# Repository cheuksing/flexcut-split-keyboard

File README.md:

# Choc 5×4 split keyboard

One identical 20-key half-PCB design, used twice switch-side up. The key field
is symmetric: cumulative column heights **0, 3, 8, 3, 0 mm**, with **19.05 mm**
pitch. Each half uses the generated solder-only **Choc V1/V2 flex footprint**,
20 bottom-side SOD-523 diodes and **five charlieplex scan nets**. The right-hand
anatomical columns reverse; the physical Choc pin patterns do not flip.

The sole PCB definition and output is **`choc5x4_panel`**, the unrouted
98.20×99.475 mm breakaway panel containing one half and the XIAO SAMD21 adapter.
Each component placement is defined once. Checks and drawings extract the half
and adapter directly from this panel. The adapter has headers, two upright USB-C
ports, series/contact isolation resistors and TVS only. All SMD assembly parts,
including the ports and matrix diodes, are on the bottom; switches and the XIAO
are fitted separately on top. No extra regulator or
active protector. Selected USB-C groups preserve identity in all four modeled
plug orientations. Scan margins, rollover and powered/unpowered fault safety
remain on [electrical hold](docs/usb-c-interface-verification.md).
Native KiCad ERC/DRC and complete case construction remain open.

## Build and review

To use the local Ergogen web interface after `npm ci`:

```sh
npm run dev
```

Open **http://127.0.0.1:8787**. The editor loads `ergogen/config.yaml` and the
project's custom switch/diode footprints. It generates key positions, outlines
and a PCB preview, with zoom/pan and YAML, SVG, DXF, JSON and KiCad downloads.
Drafts stay in memory; downloading YAML does not overwrite the project file.
Invalid edits show generation errors while clearly marking the last preview as
outdated. The checked matrix review is available from the header.

The server binds to this computer only, uses the pinned local Ergogen engine and
needs no external service. Change the port with `PORT=8788 npm run dev`. Stop it
with Ctrl+C. Web generation is a preview, not a manufacturing check: after saving
an edited configuration into the project, run `npm run review`.

Requires Node.js 22+ and Python/Shapely. Install pinned Node dependencies and the
geometry dependency once:

```sh
npm ci
python3 -m venv .venv-manufacturing
.venv-manufacturing/bin/python -m pip install -r scripts/requirements-manufacturing.txt
npm run review
```

For another Python environment, set `MANUFACTURING_PYTHON` to its interpreter.
The following are local review artifacts; the workflow uses no browser or GUI:

- [Keyboard review](build/keyboard/index.html), [layout PNG](build/keyboard/layout.png),
  [matrix PNG](build/keyboard/matrix.png), [support concepts](build/keyboard/supports.png).
- [Panel KiCad PCB](build/keyboard/choc5x4_panel.kicad_pcb) and
  [half schematic](build/keyboard/choc5x4_half.kicad_sch).
- [Directed-pair CSV](build/keyboard/matrix.csv) and [key placements](build/keyboard/keys.json).
- [All three switch footprints](build/review/index.html) and their generated
  `build/review/SwitchFlex.pretty/` library.
- [Exact-input verification](docs/manufacturing-verification.md) and
  [constraint register](docs/manufacturing-limitations.md).
- [Actual panel](build/keyboard/panel-fit.svg), [adapter placement](build/keyboard/adapter.svg),
  [adapter schematic](build/keyboard/adapter.kicad_sch).
  Mount the XIAO on two six-pin headers after detaching the adapter; the module overhangs the carrier.

`npm run check` rebuilds all footprints and the keyboard, tests actual schematic
connectivity against PCB pad nets, and checks all three 3×3 fixtures **plus the
complete staggered half, adapter and actual panel**. It also rechecks derived continuous gasket/rib concepts.
`npm run review` runs that full gate before emitting drawings. Ordinary drawing
checks do not establish native KiCad, CAM, fatigue or price approval.

`npm run check:interface` writes the USB-C electrical report and exits nonzero
while scan margins, rollover and protection remain unresolved.
This electrical release gate is separate from the geometry checks above.

`npm run build:keyboard` emits CAD without the manufacturing gate. Use the npm
runner: it sets PCB thickness to **1.2 mm**; the bare Ergogen KiCad 8 CLI template
defaults to 1.6 mm. Generated `*.kicad*` files under `build/` are committed so
they can be previewed in KiCanvas; other build outputs remain ignored and can be
recreated with `npm run review`.

## Design sources

```text
ergogen/config.yaml               Sole panel PCB definition; shared half/adapter outlines
ergogen/footprints/choc.js         Generated Choc V1/V2 footprint, unchanged pin/cut geometry
ergogen/footprints/diode_sod523.js  Bottom-side diode land pattern; candidate SKU pending
ergogen/fixtures/                  Preserved original single-key coupon configuration
scripts/build-keyboard.js          Ergogen runner, thickness, CAD, net map and local library
scripts/lib/keyboard-schematic.js  Embedded-symbol KiCad matrix schematic generator
scripts/lib/keyboard.js            Readers and electrical connectivity checks
scripts/lib/board-views.js         Extract half/adapter review geometry from the panel
scripts/check-keyboard.py          Actual staggered-board and support geometry screens
scripts/lib/manufacturing-rules.json  Numeric fabrication/project guards
scripts/build-keyboard-review.js   Offline SVG/PNG/HTML keyboard review
scripts/serve-ergogen.js           Loopback-only web editor and in-memory generation API
web/                              Local YAML editor, interactive preview and downloads
keyboard-flex-study/               Original per-key suspension research and drawings
docs/keyboard.md                  Circuit, reuse, placement and remaining work
```

The library also retains KS-33 and MX footprints. Edit switch geometry in
`scripts/lib/switches.js` and `scripts/lib/footprint-template.js`, then regenerate
and check. Do not hand-edit generated switch modules or scale their flex cuts to
smaller Choc pitch. All switch solder copper/mask stays on B.Cu/B.Mask only;
electrical and V2 mechanical holes remain plated, plastic posts unplated, and the
V2 support unnumbered/unconnected.

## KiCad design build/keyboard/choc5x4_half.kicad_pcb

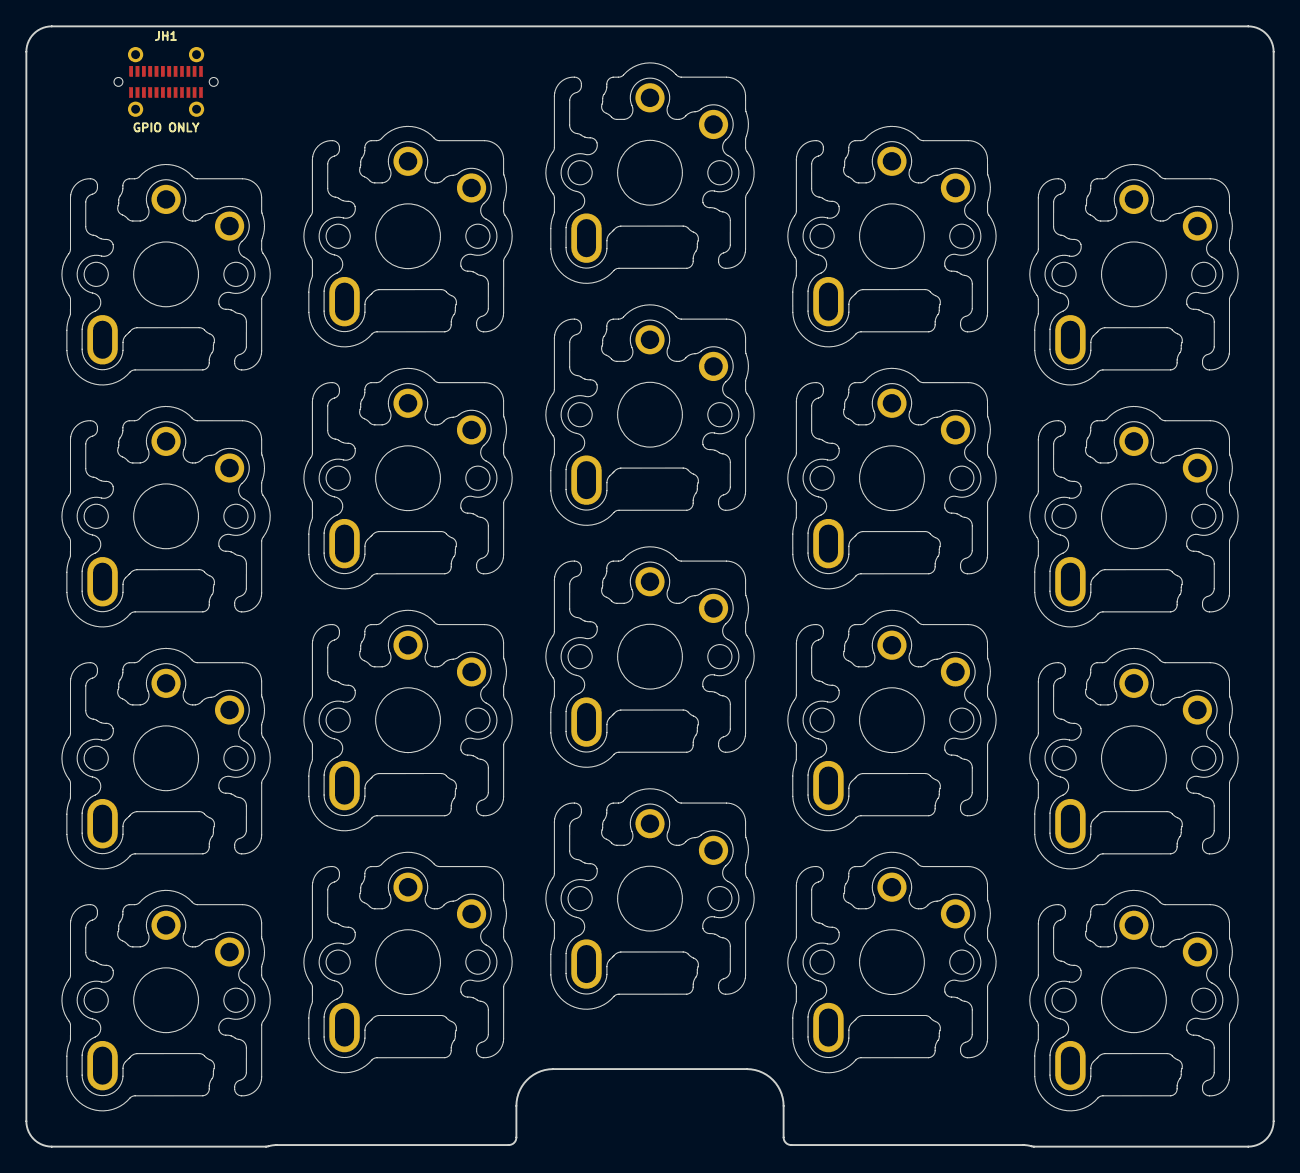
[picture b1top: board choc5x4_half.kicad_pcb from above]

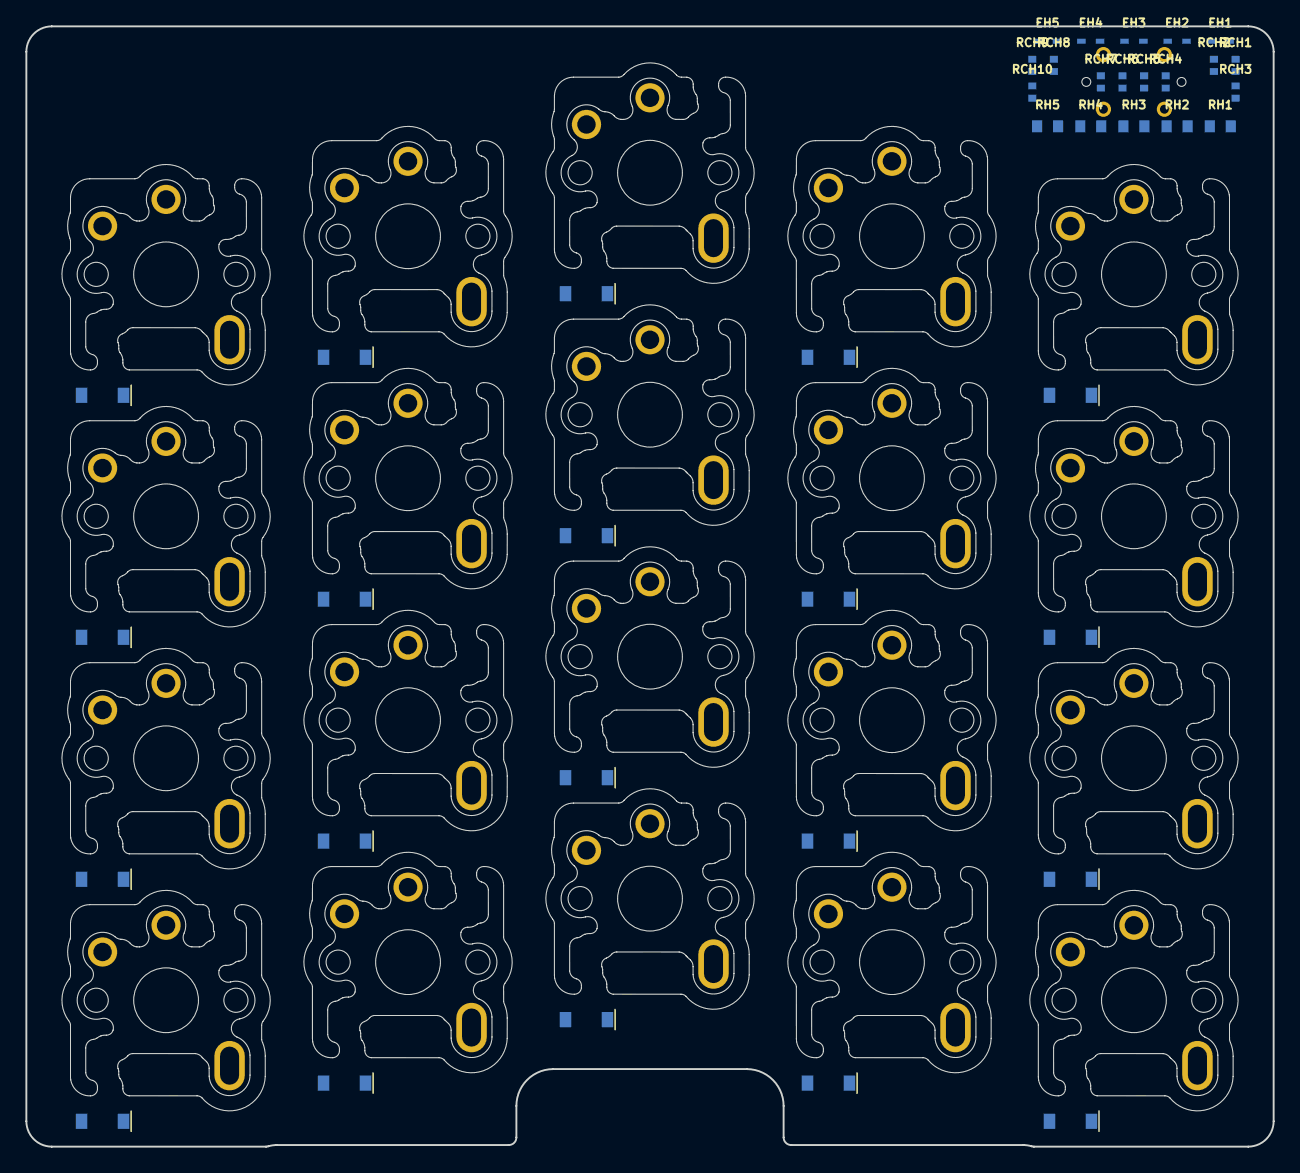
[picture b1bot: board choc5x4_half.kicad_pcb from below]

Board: 2 copper layers, 98.2 x 88.2 mm, 61 parts (40 on the bottom side), 41 nets, no tracks yet.

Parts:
D1, D2, D3, D4, D5, D6, D7, D8, D9, D10, D11, D12, D13, D14, D15, D16, D17, D18, D19, D20: 1N4148W; diode_sod123
EH1, EH2, EH3, EH4, EH5: TPD1E05U06DYA; sod523
JH1: USB4115-03-C / GPIO ONLY; usb4115
RCH1, RCH2, RCH3, RCH4, RCH5, RCH6, RCH7, RCH8, RCH9, RCH10: 1k contact isolation; r0402
RH1, RH2, RH3, RH4, RH5: 1k; r0603
SW1, SW2, SW3, SW4, SW5, SW6, SW7, SW8, SW9, SW10, SW11, SW12, SW13, SW14, SW15, SW16, SW17, SW18, SW19, SW20: Kailh Choc V1 / V2; choc

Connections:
HC0: EH1.1, RCH1.2, RCH2.2, RH1.1
HC1: EH2.1, RCH3.2, RCH4.2, RH2.1
HC2: EH3.1, RCH5.2, RCH6.2, RH3.1
HC3: EH4.1, RCH7.2, RCH8.2, RH4.1
HC4: EH5.1, RCH9.2, RCH10.2, RH5.1
H_A2: JH1.A2, RCH1.1
H_A3: JH1.A3, RCH3.1
H_A8: JH1.A8, RCH9.1
H_A10: JH1.A10, RCH5.1
H_A11: JH1.A11, RCH7.1
H_B2: JH1.B2, RCH2.1
H_B3: JH1.B3, RCH4.1
H_B8: JH1.B8, RCH10.1
H_B10: JH1.B10, RCH6.1
H_B11: JH1.B11, RCH8.1
K_COL0_ROW0: D4.2, SW4.2
K_COL0_ROW1: D3.2, SW3.2
K_COL0_ROW2: D2.2, SW2.2
K_COL0_ROW3: D1.2, SW1.2
K_COL1_ROW0: D8.2, SW8.2
K_COL1_ROW1: D7.2, SW7.2
K_COL1_ROW2: D6.2, SW6.2
K_COL1_ROW3: D5.2, SW5.2
K_COL2_ROW0: D12.2, SW12.2
K_COL2_ROW1: D11.2, SW11.2
K_COL2_ROW2: D10.2, SW10.2
K_COL2_ROW3: D9.2, SW9.2
K_COL3_ROW0: D16.2, SW16.2
K_COL3_ROW1: D15.2, SW15.2
K_COL3_ROW2: D14.2, SW14.2
K_COL3_ROW3: D13.2, SW13.2
K_COL4_ROW0: D20.2, SW20.2
K_COL4_ROW1: D19.2, SW19.2
K_COL4_ROW2: D18.2, SW18.2
K_COL4_ROW3: D17.2, SW17.2
P0: D8.1, D11.1, D14.1, D17.1, RH1.2, SW1.1, SW2.1, SW3.1, SW4.1
P1: D1.1, D12.1, D15.1, D18.1, RH2.2, SW5.1, SW6.1, SW7.1, SW8.1
P2: D2.1, D5.1, D16.1, D19.1, RH3.2, SW9.1, SW10.1, SW11.1, SW12.1
P3: D3.1, D6.1, D9.1, D20.1, RH4.2, SW13.1, SW14.1, SW15.1, SW16.1
P4: D4.1, D7.1, D10.1, D13.1, RH5.2, SW17.1, SW18.1, SW19.1, SW20.1
SHIELD_H: EH1.2, EH2.2, EH3.2, EH4.2, EH5.2, JH1.S1, JH1.S2, JH1.S3, JH1.S4

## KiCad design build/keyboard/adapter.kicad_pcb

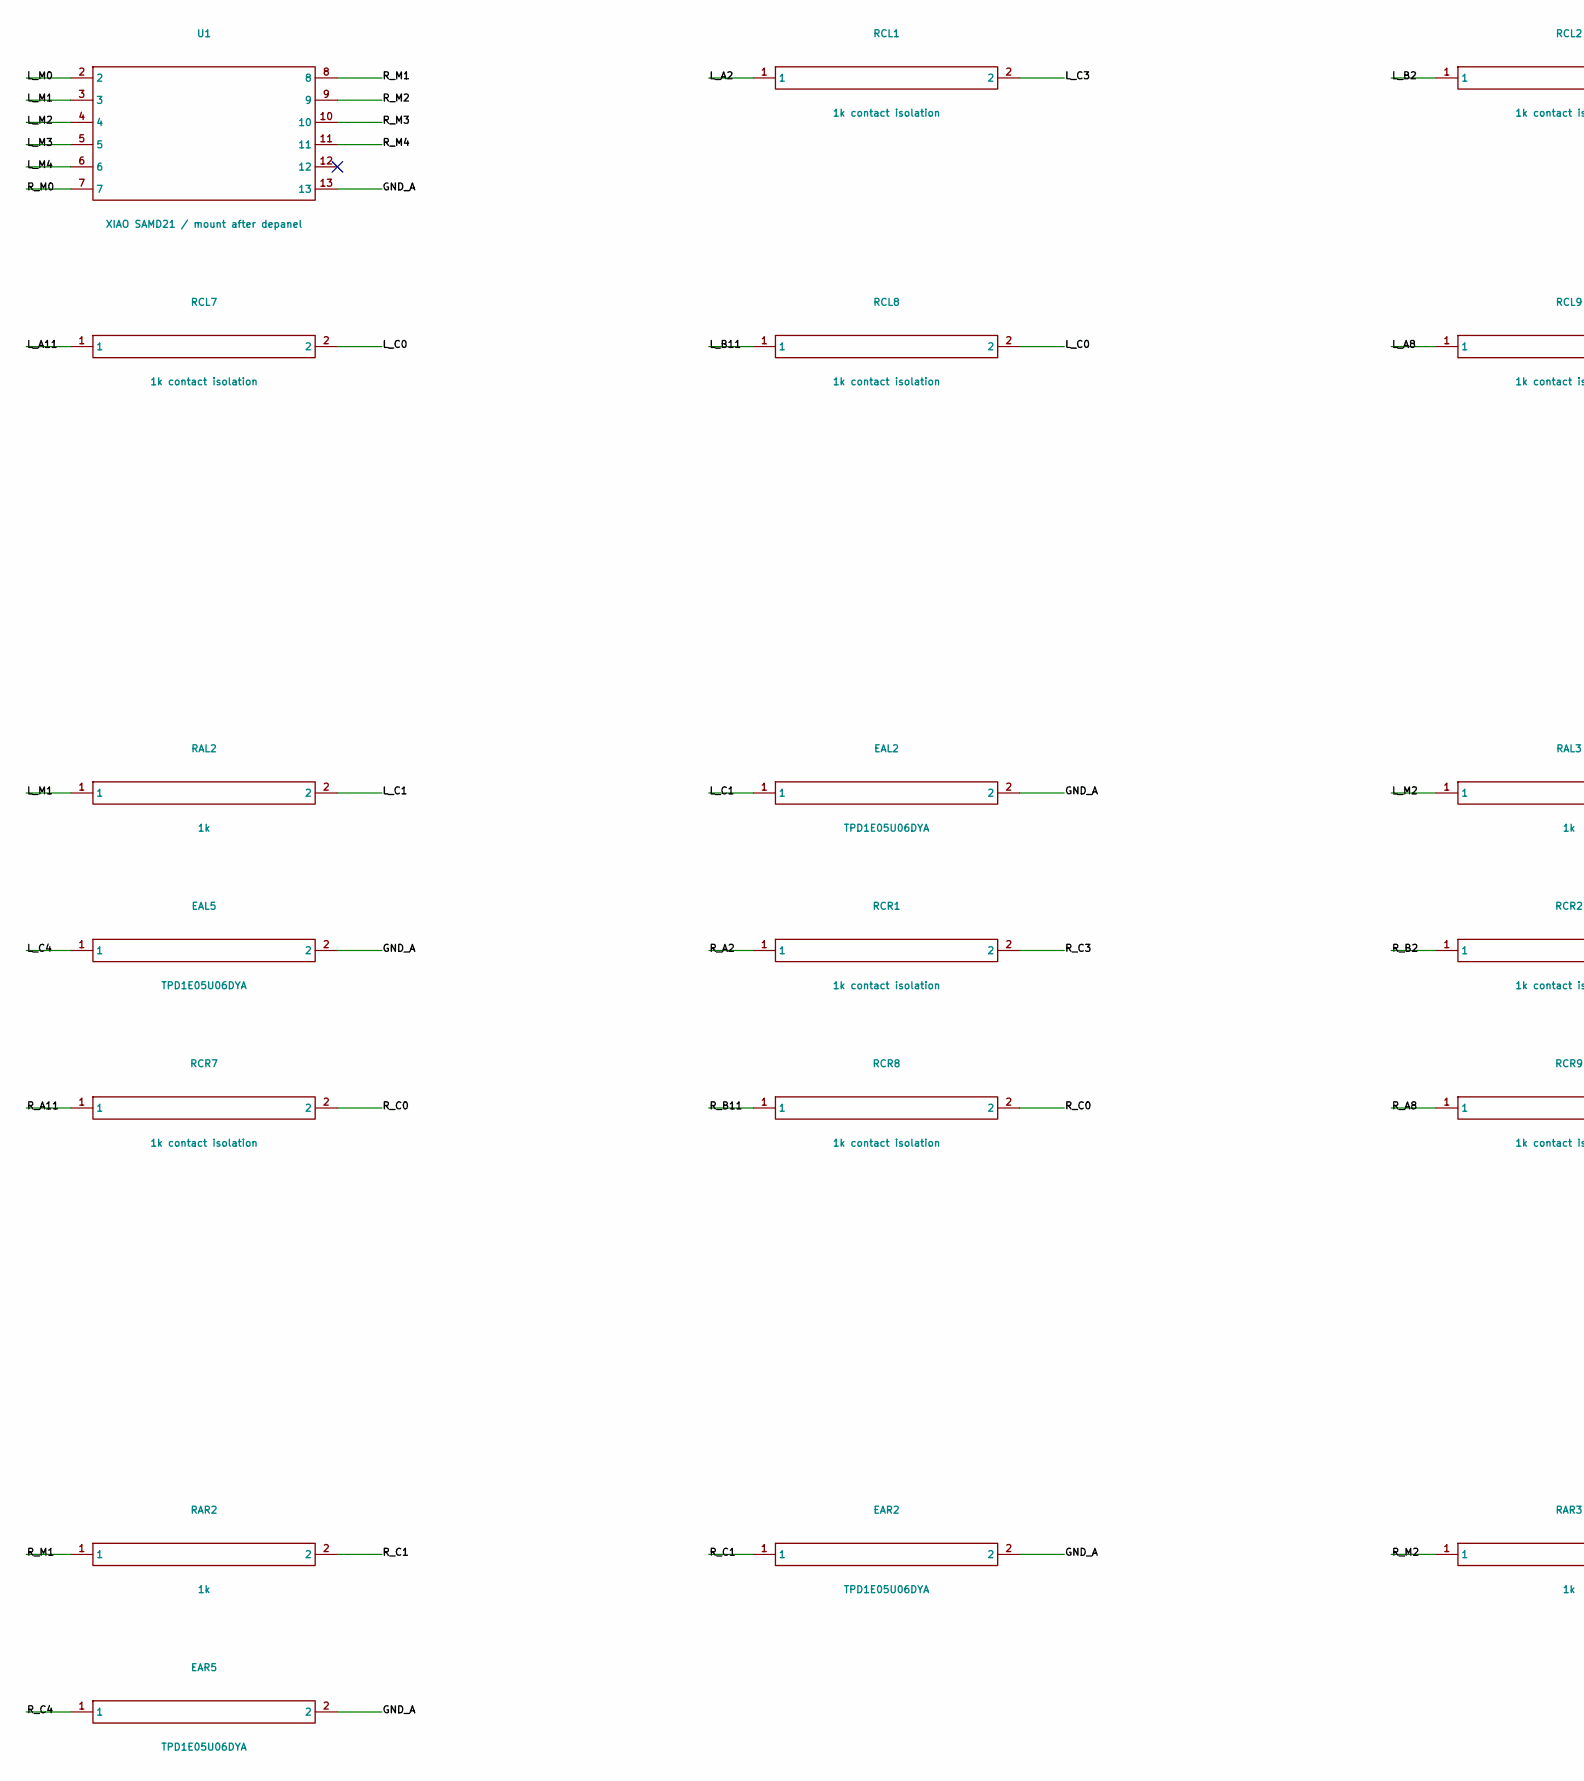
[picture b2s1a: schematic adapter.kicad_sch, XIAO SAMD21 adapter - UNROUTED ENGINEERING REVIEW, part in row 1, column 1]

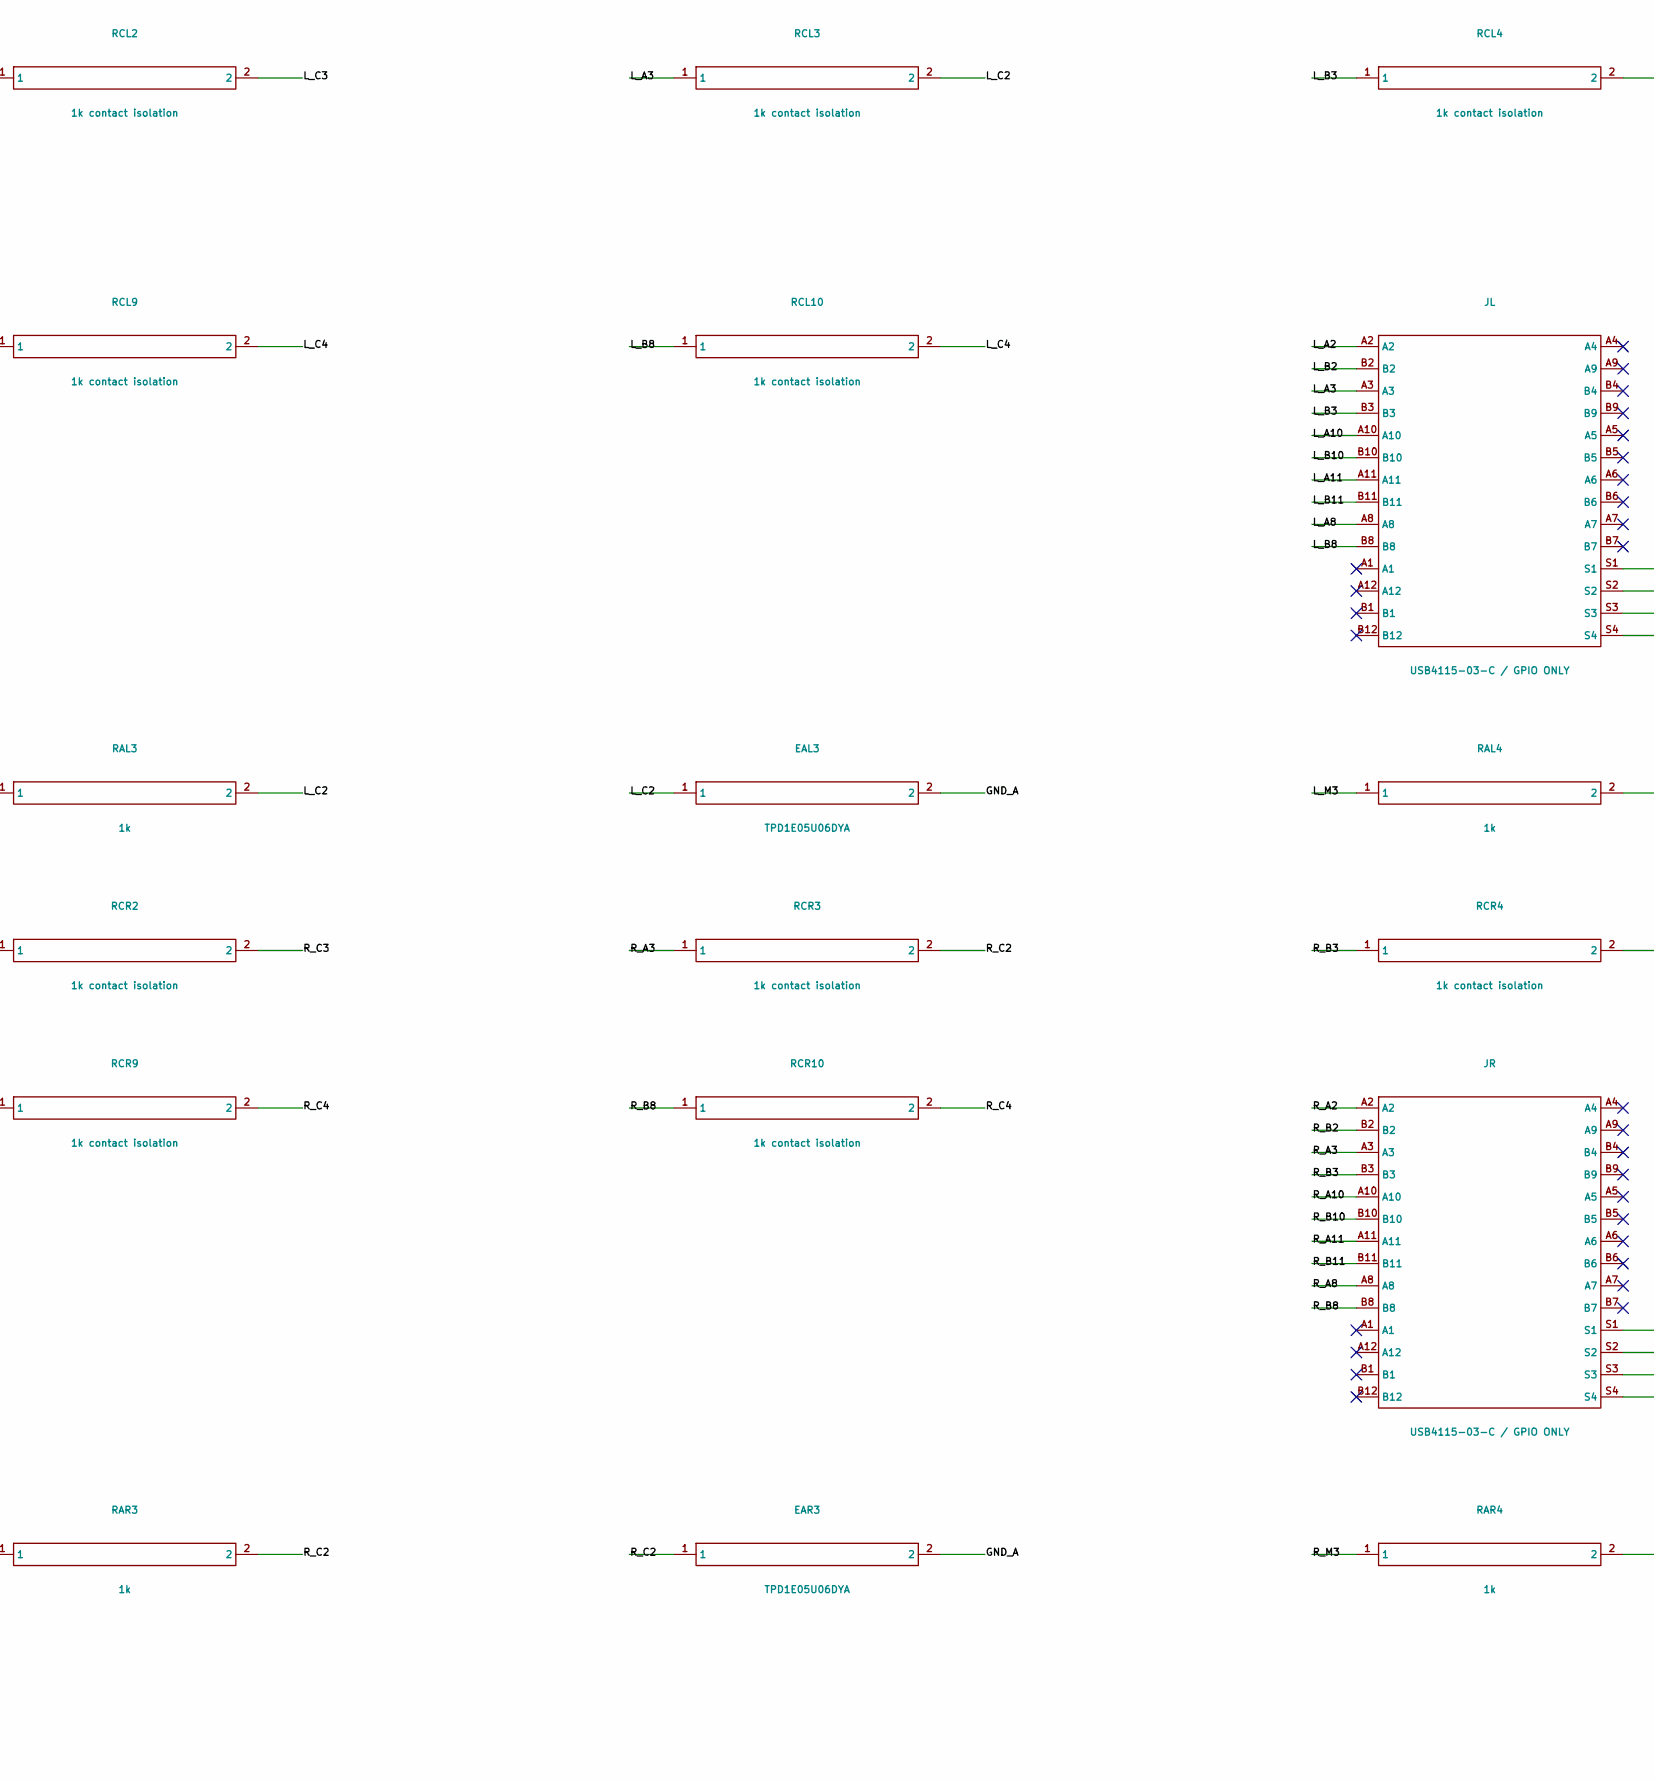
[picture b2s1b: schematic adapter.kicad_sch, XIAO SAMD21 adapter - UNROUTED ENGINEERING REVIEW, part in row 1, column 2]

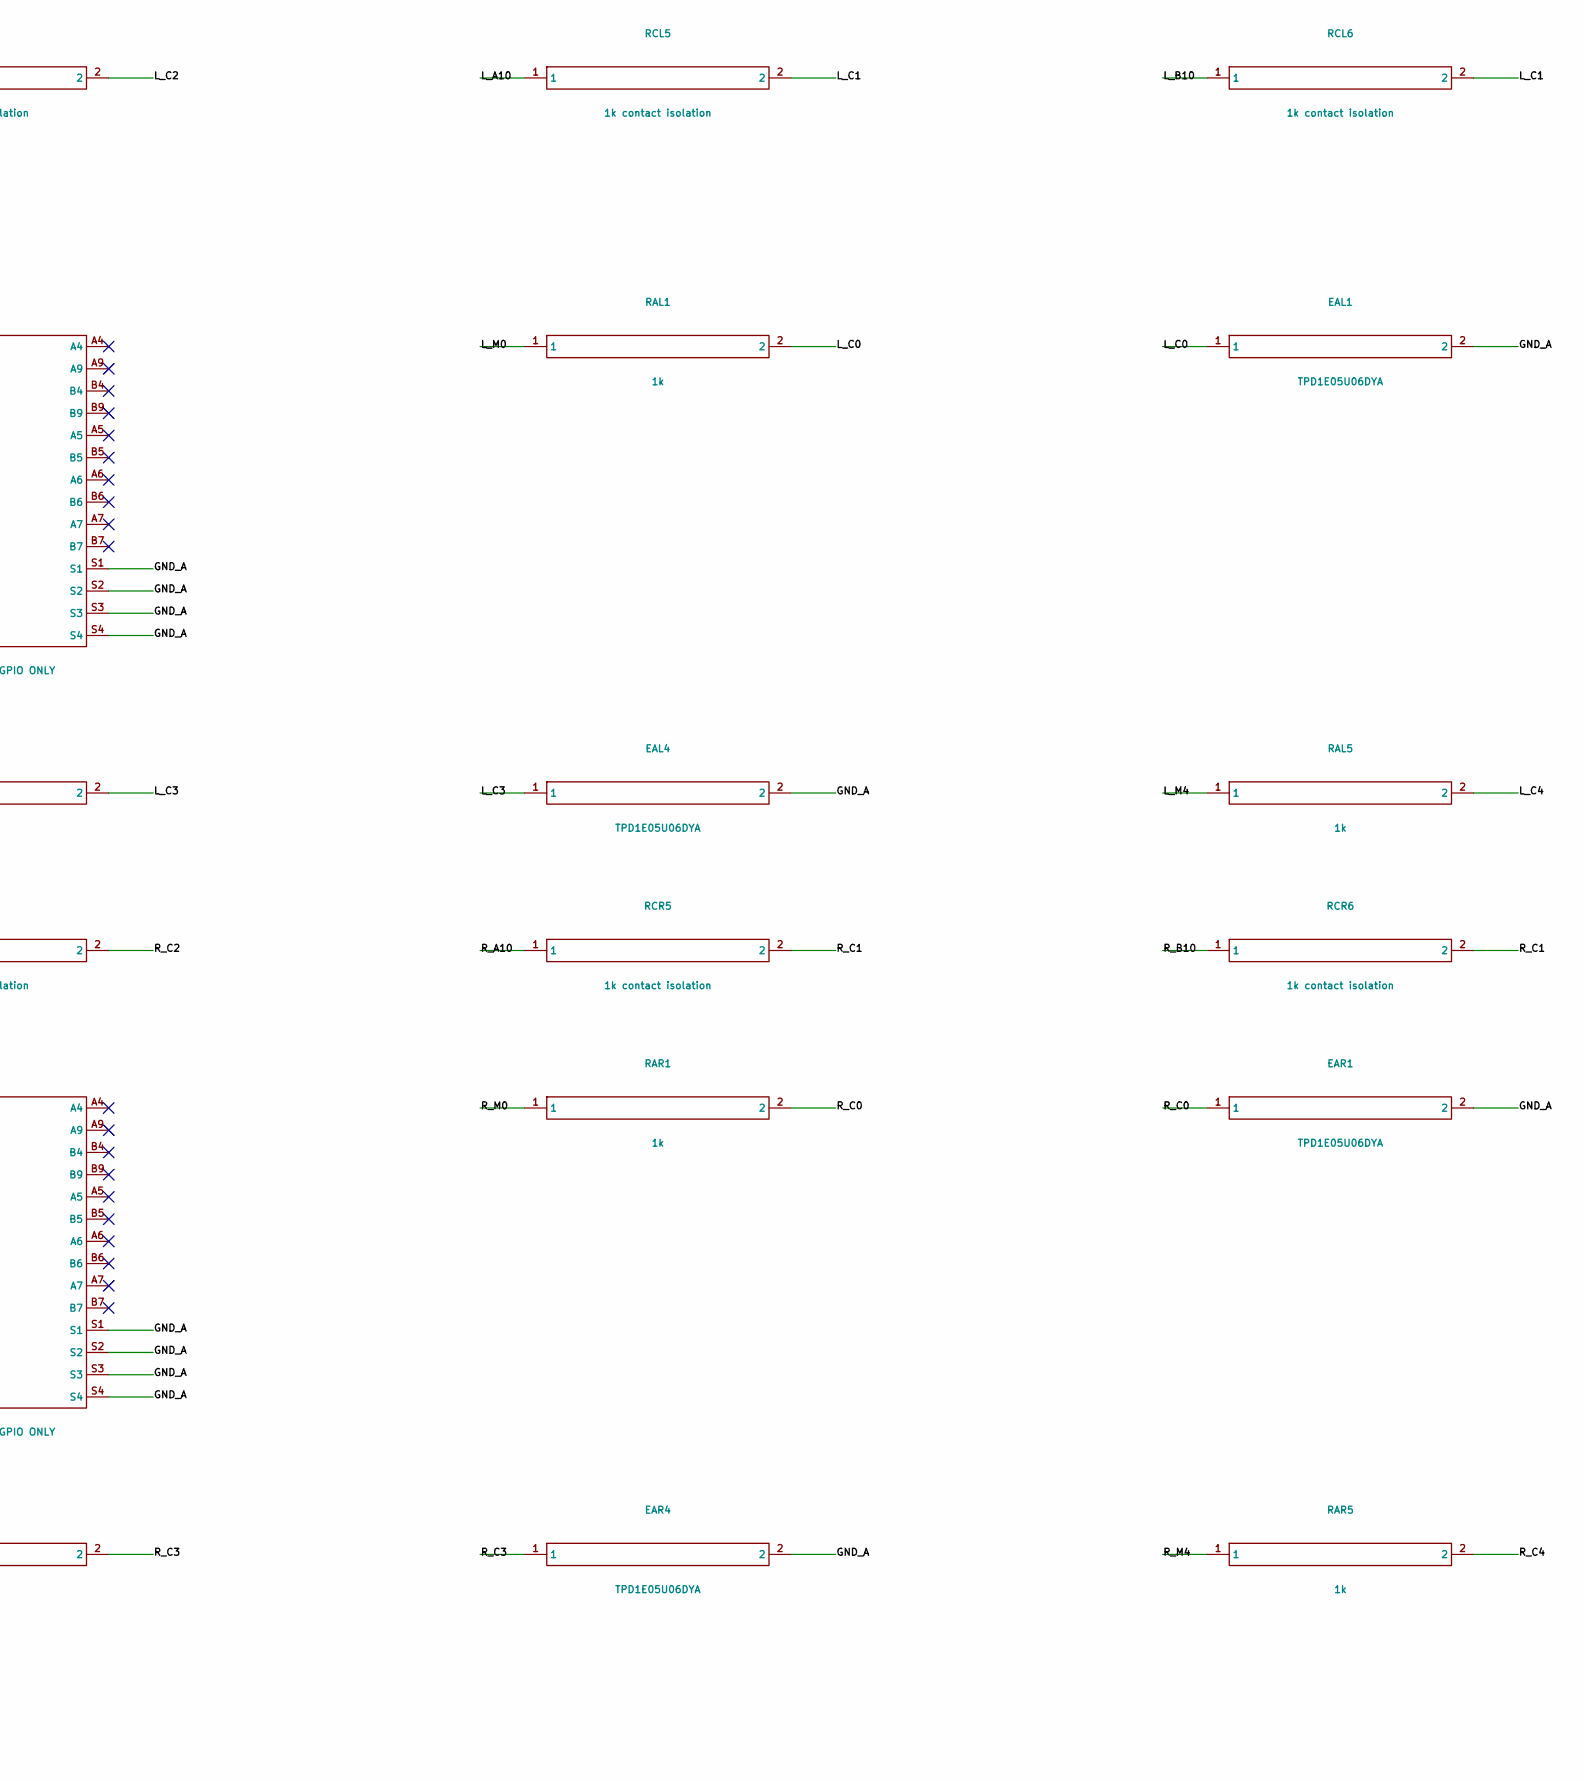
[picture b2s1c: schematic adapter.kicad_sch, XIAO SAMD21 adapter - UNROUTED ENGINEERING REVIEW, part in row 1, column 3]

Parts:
EAL1, EAL2, EAL3, EAL4, EAL5: TPD1E05U06DYA; sod523
EAR1, EAR2, EAR3, EAR4, EAR5: TPD1E05U06DYA; sod523
JL: USB4115-03-C / GPIO ONLY; usb4115
JR: USB4115-03-C / GPIO ONLY; usb4115
RAL1, RAL2, RAL3, RAL4, RAL5: 1k; r0603
RAR1, RAR2, RAR3, RAR4, RAR5: 1k; r0603
RCL1, RCL2, RCL3, RCL4, RCL5, RCL6, RCL7, RCL8, RCL9, RCL10: 1k contact isolation; r0402
RCR1, RCR2, RCR3, RCR4, RCR5, RCR6, RCR7, RCR8, RCR9, RCR10: 1k contact isolation; r0402
U1: XIAO SAMD21 / mount after depanel; xiao12

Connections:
GND_A: EAL1.2, EAL2.2, EAL3.2, EAL4.2, EAL5.2, EAR1.2, EAR2.2, EAR3.2, EAR4.2, EAR5.2, JL.S1, JL.S2, JL.S3, JL.S4, JR.S1, JR.S2, JR.S3, JR.S4, U1.13
L_A2: JL.A2, RCL1.1
L_A3: JL.A3, RCL3.1
L_A8: JL.A8, RCL9.1
L_A10: JL.A10, RCL5.1
L_A11: JL.A11, RCL7.1
L_B2: JL.B2, RCL2.1
L_B3: JL.B3, RCL4.1
L_B8: JL.B8, RCL10.1
L_B10: JL.B10, RCL6.1
L_B11: JL.B11, RCL8.1
L_C0: EAL1.1, RAL1.2, RCL7.2, RCL8.2
L_C1: EAL2.1, RAL2.2, RCL5.2, RCL6.2
L_C2: EAL3.1, RAL3.2, RCL3.2, RCL4.2
L_C3: EAL4.1, RAL4.2, RCL1.2, RCL2.2
L_C4: EAL5.1, RAL5.2, RCL9.2, RCL10.2
L_M0: RAL1.1, U1.2
L_M1: RAL2.1, U1.3
L_M2: RAL3.1, U1.4
L_M3: RAL4.1, U1.5
L_M4: RAL5.1, U1.6
R_A2: JR.A2, RCR1.1
R_A3: JR.A3, RCR3.1
R_A8: JR.A8, RCR9.1
R_A10: JR.A10, RCR5.1
R_A11: JR.A11, RCR7.1
R_B2: JR.B2, RCR2.1
R_B3: JR.B3, RCR4.1
R_B8: JR.B8, RCR10.1
R_B10: JR.B10, RCR6.1
R_B11: JR.B11, RCR8.1
R_C0: EAR1.1, RAR1.2, RCR7.2, RCR8.2
R_C1: EAR2.1, RAR2.2, RCR5.2, RCR6.2
R_C2: EAR3.1, RAR3.2, RCR3.2, RCR4.2
R_C3: EAR4.1, RAR4.2, RCR1.2, RCR2.2
R_C4: EAR5.1, RAR5.2, RCR9.2, RCR10.2
R_M0: RAR1.1, U1.7
R_M1: RAR2.1, U1.8
R_M2: RAR3.1, U1.9
R_M3: RAR4.1, U1.10
R_M4: RAR5.1, U1.11

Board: 2 copper layers, 43 parts (40 on the bottom side), 41 nets, no tracks yet.

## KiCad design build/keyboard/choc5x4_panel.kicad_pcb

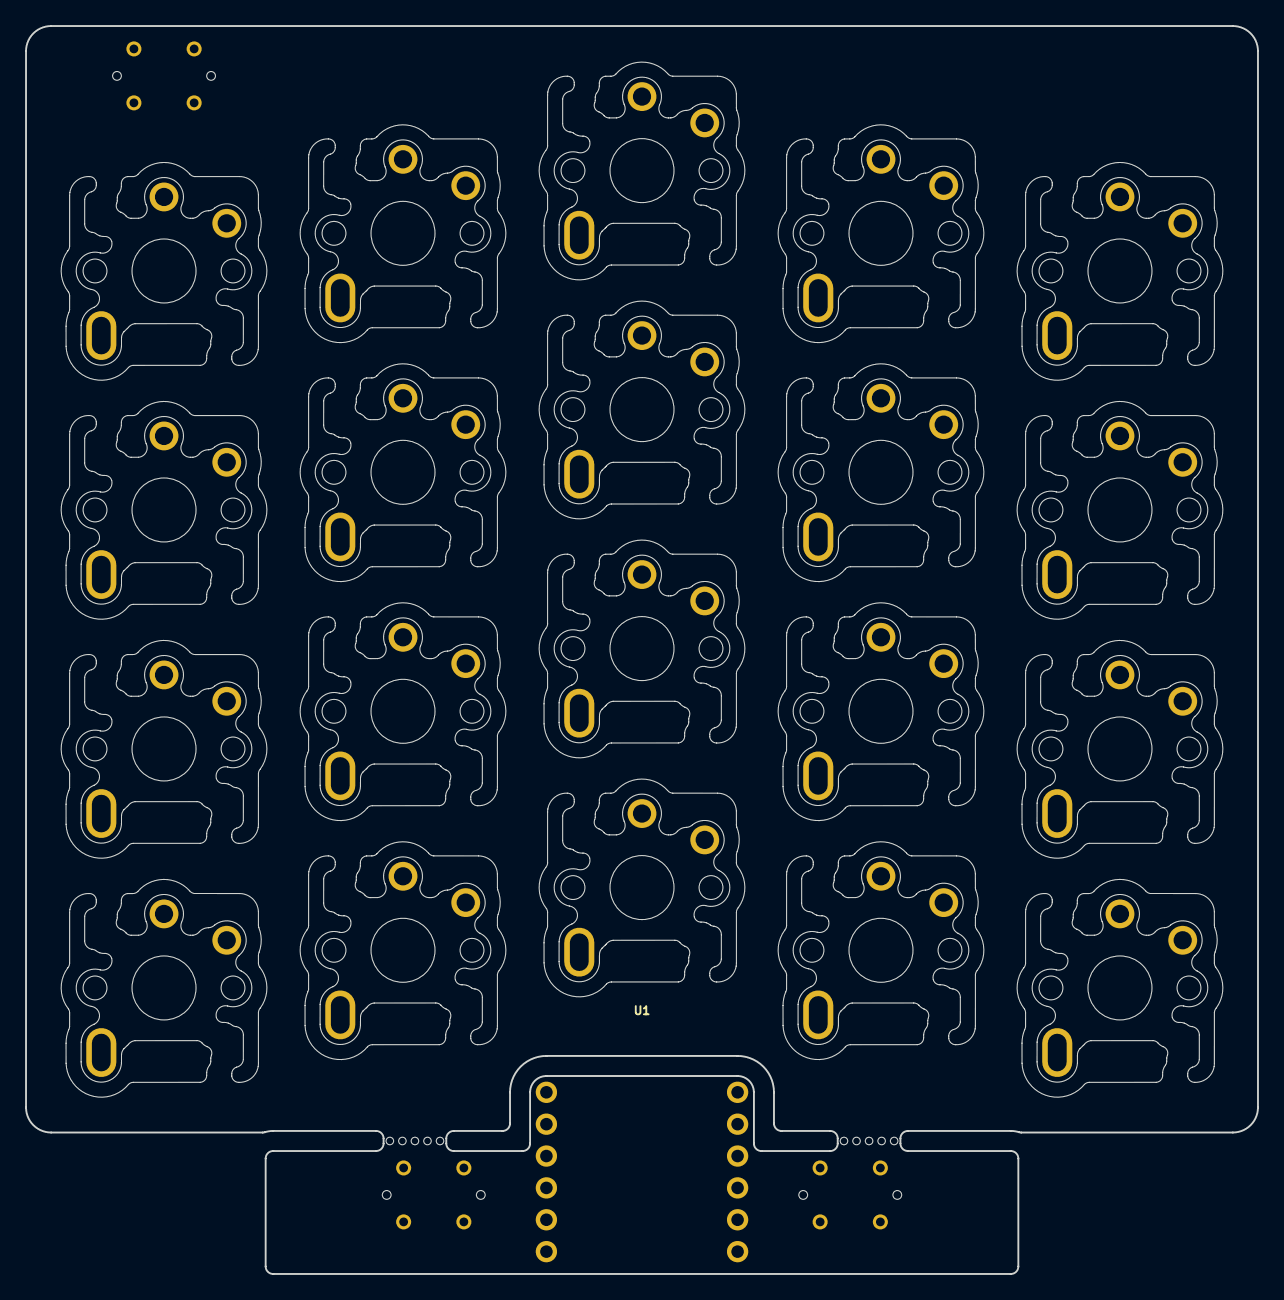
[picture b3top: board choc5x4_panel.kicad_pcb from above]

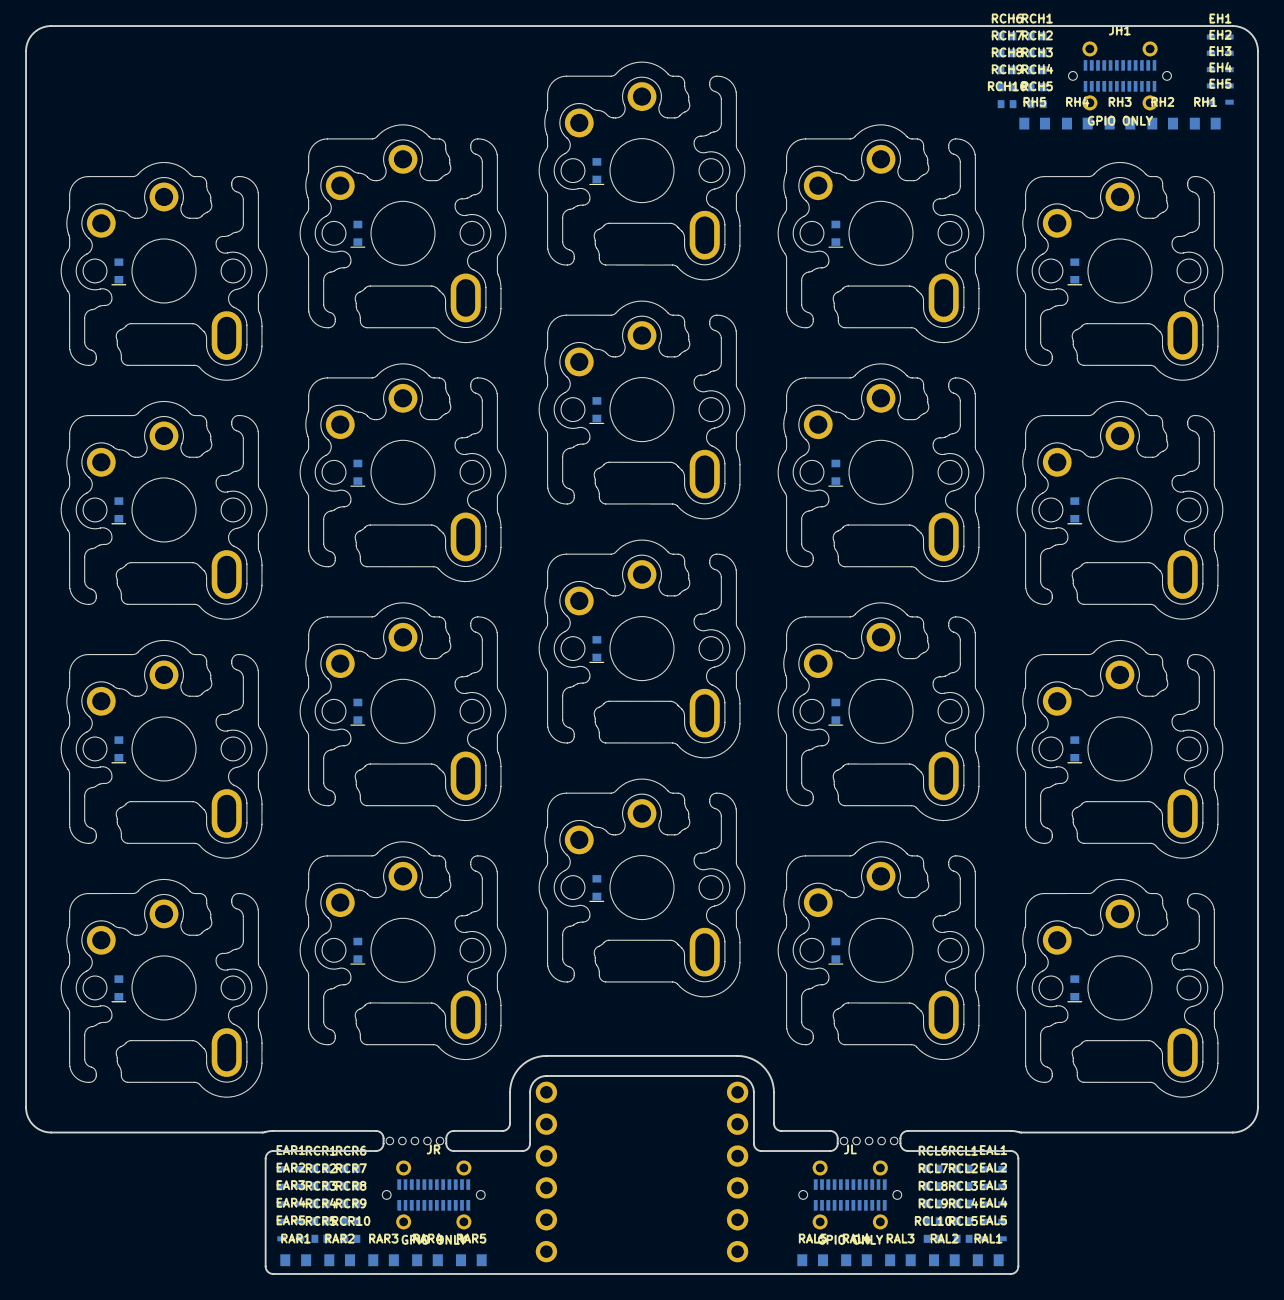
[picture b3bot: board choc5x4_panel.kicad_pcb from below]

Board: 2 copper layers, 98.2 x 99.5 mm, 106 parts (83 on the bottom side), 82 nets, no tracks yet.

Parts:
D1, D2, D3, D4, D5, D6, D7, D8, D9, D10, D11, D12, D13, D14, D15, D16, D17, D18, D19, D20: 1N4148WT; diode_sod523
EAL1, EAL2, EAL3, EAL4, EAL5: TPD1E05U06DYA; sod523
EAR1, EAR2, EAR3, EAR4, EAR5: TPD1E05U06DYA; sod523
EH1, EH2, EH3, EH4, EH5: TPD1E05U06DYA; sod523
JH1: USB4115-03-C / GPIO ONLY; usb4115
JL: USB4115-03-C / GPIO ONLY; usb4115
JR: USB4115-03-C / GPIO ONLY; usb4115
MB1, MB2: mouse_bites
RAL1, RAL2, RAL3, RAL4, RAL5: 1k; r0603
RAR1, RAR2, RAR3, RAR4, RAR5: 1k; r0603
RCH1, RCH2, RCH3, RCH4, RCH5, RCH6, RCH7, RCH8, RCH9, RCH10: 1k contact isolation; r0402
RCL1, RCL2, RCL3, RCL4, RCL5, RCL6, RCL7, RCL8, RCL9, RCL10: 1k contact isolation; r0402
RCR1, RCR2, RCR3, RCR4, RCR5, RCR6, RCR7, RCR8, RCR9, RCR10: 1k contact isolation; r0402
RH1, RH2, RH3, RH4, RH5: 1k; r0603
SW1, SW2, SW3, SW4, SW5, SW6, SW7, SW8, SW9, SW10, SW11, SW12, SW13, SW14, SW15, SW16, SW17, SW18, SW19, SW20: Kailh Choc V1 / V2; choc
U1: XIAO SAMD21 / mount after depanel; xiao12

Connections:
GND_A: EAL1.2, EAL2.2, EAL3.2, EAL4.2, EAL5.2, EAR1.2, EAR2.2, EAR3.2, EAR4.2, EAR5.2, JL.S1, JL.S2, JL.S3, JL.S4, JR.S1, JR.S2, JR.S3, JR.S4, U1.13
HC0: EH1.1, RCH1.2, RCH2.2, RH1.1
HC1: EH2.1, RCH3.2, RCH4.2, RH2.1
HC2: EH3.1, RCH5.2, RCH6.2, RH3.1
HC3: EH4.1, RCH7.2, RCH8.2, RH4.1
HC4: EH5.1, RCH9.2, RCH10.2, RH5.1
H_A2: JH1.A2, RCH1.1
H_A3: JH1.A3, RCH3.1
H_A8: JH1.A8, RCH9.1
H_A10: JH1.A10, RCH5.1
H_A11: JH1.A11, RCH7.1
H_B2: JH1.B2, RCH2.1
H_B3: JH1.B3, RCH4.1
H_B8: JH1.B8, RCH10.1
H_B10: JH1.B10, RCH6.1
H_B11: JH1.B11, RCH8.1
K_COL0_ROW0: D4.2, SW4.2
K_COL0_ROW1: D3.2, SW3.2
K_COL0_ROW2: D2.2, SW2.2
K_COL0_ROW3: D1.2, SW1.2
K_COL1_ROW0: D8.2, SW8.2
K_COL1_ROW1: D7.2, SW7.2
K_COL1_ROW2: D6.2, SW6.2
K_COL1_ROW3: D5.2, SW5.2
K_COL2_ROW0: D12.2, SW12.2
K_COL2_ROW1: D11.2, SW11.2
K_COL2_ROW2: D10.2, SW10.2
K_COL2_ROW3: D9.2, SW9.2
K_COL3_ROW0: D16.2, SW16.2
K_COL3_ROW1: D15.2, SW15.2
K_COL3_ROW2: D14.2, SW14.2
K_COL3_ROW3: D13.2, SW13.2
K_COL4_ROW0: D20.2, SW20.2
K_COL4_ROW1: D19.2, SW19.2
K_COL4_ROW2: D18.2, SW18.2
K_COL4_ROW3: D17.2, SW17.2
L_A2: JL.A2, RCL1.1
L_A3: JL.A3, RCL3.1
L_A8: JL.A8, RCL9.1
L_A10: JL.A10, RCL5.1
L_A11: JL.A11, RCL7.1
L_B2: JL.B2, RCL2.1
L_B3: JL.B3, RCL4.1
L_B8: JL.B8, RCL10.1
L_B10: JL.B10, RCL6.1
L_B11: JL.B11, RCL8.1
L_C0: EAL1.1, RAL1.2, RCL7.2, RCL8.2
L_C1: EAL2.1, RAL2.2, RCL5.2, RCL6.2
L_C2: EAL3.1, RAL3.2, RCL3.2, RCL4.2
L_C3: EAL4.1, RAL4.2, RCL1.2, RCL2.2
L_C4: EAL5.1, RAL5.2, RCL9.2, RCL10.2
L_M0: RAL1.1, U1.2
L_M1: RAL2.1, U1.3
L_M2: RAL3.1, U1.4
L_M3: RAL4.1, U1.5
L_M4: RAL5.1, U1.6
P0: D8.1, D11.1, D14.1, D17.1, RH1.2, SW1.1, SW2.1, SW3.1, SW4.1
P1: D1.1, D12.1, D15.1, D18.1, RH2.2, SW5.1, SW6.1, SW7.1, SW8.1
P2: D2.1, D5.1, D16.1, D19.1, RH3.2, SW9.1, SW10.1, SW11.1, SW12.1
P3: D3.1, D6.1, D9.1, D20.1, RH4.2, SW13.1, SW14.1, SW15.1, SW16.1
P4: D4.1, D7.1, D10.1, D13.1, RH5.2, SW17.1, SW18.1, SW19.1, SW20.1
R_A2: JR.A2, RCR1.1
R_A3: JR.A3, RCR3.1
R_A8: JR.A8, RCR9.1
R_A10: JR.A10, RCR5.1
R_A11: JR.A11, RCR7.1
R_B2: JR.B2, RCR2.1
R_B3: JR.B3, RCR4.1
R_B8: JR.B8, RCR10.1
R_B10: JR.B10, RCR6.1
R_B11: JR.B11, RCR8.1
R_C0: EAR1.1, RAR1.2, RCR7.2, RCR8.2
R_C1: EAR2.1, RAR2.2, RCR5.2, RCR6.2
R_C2: EAR3.1, RAR3.2, RCR3.2, RCR4.2
R_C3: EAR4.1, RAR4.2, RCR1.2, RCR2.2
R_C4: EAR5.1, RAR5.2, RCR9.2, RCR10.2
R_M0: RAR1.1, U1.7
R_M1: RAR2.1, U1.8
R_M2: RAR3.1, U1.9
R_M3: RAR4.1, U1.10
R_M4: RAR5.1, U1.11
SHIELD_H: EH1.2, EH2.2, EH3.2, EH4.2, EH5.2, JH1.S1, JH1.S2, JH1.S3, JH1.S4
